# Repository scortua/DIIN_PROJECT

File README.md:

# Proyecto CNC para Cuidado de Plantulas en Vivero

Este proyecto consiste en desarrollar una máquina CNC capaz de cuidar plantulas en un vivero, utilizando motores, materiales reciclables y económicos, incorporando inteligencia artificial y sensores.

## Objetivos
- Automatizar tareas de cuidado en el vivero.
- Optimizar el uso de recursos utilizando materiales reciclables y de bajo costo.
- Integrar sensores para monitorear las condiciones ambientales y de crecimiento de las plantulas.
- Utilizar técnicas de IA para la toma de decisiones en tiempo real.

## Componentes Principales

### Hardware
- **Motores y actuadores:** Responsables del movimiento y la acción precisa en el cuidado de las plantulas.
- **Sensores:** 
    - Sensores de humedad y temperatura para medir las condiciones ambientales.
    - Sensores de luz para asegurar niveles adecuados de iluminación.
- **Materiales reciclables:** Estructuras y componentes fabricados con materiales reutilizados y económicos.
    
### Software
- **Control CNC:** Algoritmos para la operación y movimiento controlado de la máquina.
- **Inteligencia Artificial:** 
    - Procesamiento de datos de sensores.
    - Toma de decisiones automáticas para mejorar el crecimiento de las plantulas.
- **Interfaz de usuario:** Herramienta para monitorear y configurar el sistema en tiempo real.

## Funcionamiento del Sistema

1. **Monitoreo:**  
     Los sensores recogen datos sobre humedad, temperatura y luz.  
2. **Análisis:**  
     La IA analiza la información recopilada para identificar las necesidades de cada plantula.
3. **Acción:**  
     El CNC ejecuta movimientos precisos para crear condiciones óptimas: ajustar la dosificación de agua, mover elementos o modificar la iluminación.
4. **Retroalimentación:**  
     El sistema ajusta sus acciones de forma continua, basándose en los datos en tiempo real.

## Beneficios
- Fomenta el uso de tecnologías sostenibles.
- Aumenta la eficiencia en el cuidado de plantulas.
- Reduce costos mediante el uso de materiales reciclables y componentes económicos.
- Optimiza el crecimiento y la salud de las plantas a través de decisiones basadas en datos.

Este proyecto representa un avance significativo en la integración de la robótica y la inteligencia artificial en la agricultura, proporcionando soluciones innovadoras y sostenibles para el cuidado de viveros.

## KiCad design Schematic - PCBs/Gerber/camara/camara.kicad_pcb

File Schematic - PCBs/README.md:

# Proyecto DIIN
 En este repositorio se encontrara los esquematicos, diseño de PCB's,  programas, etc; sobre el proyecto de CNC que cuide plantulas.

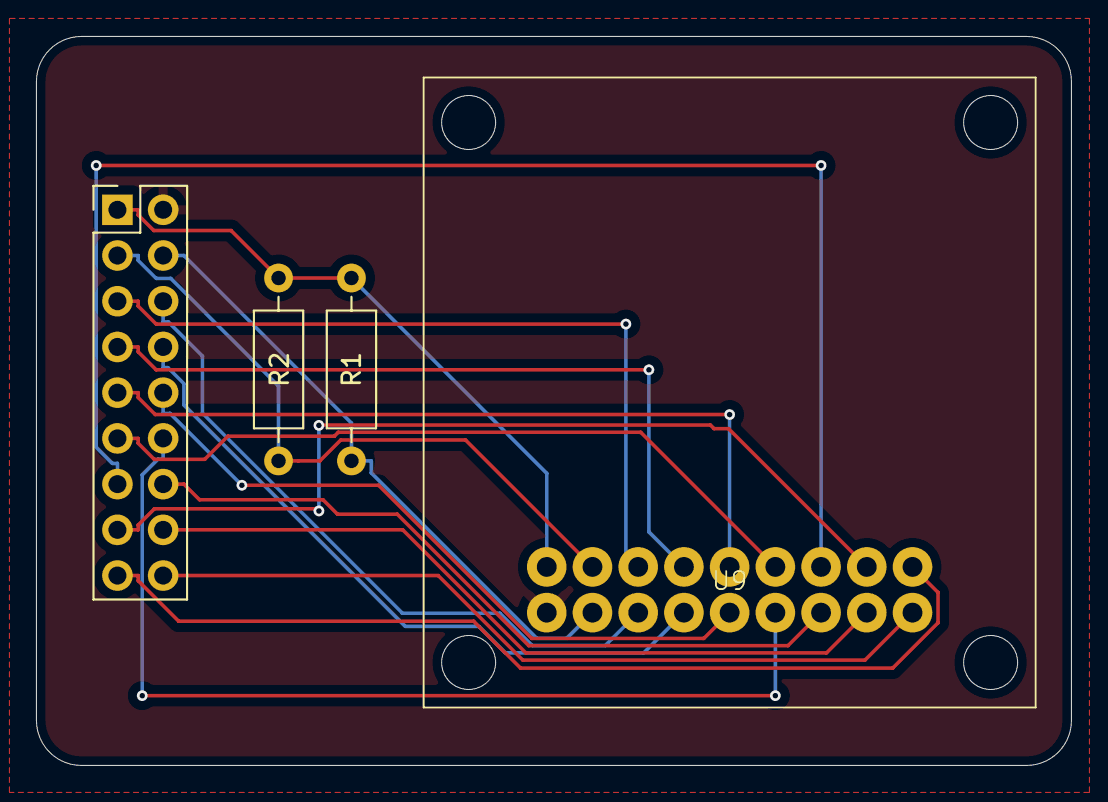
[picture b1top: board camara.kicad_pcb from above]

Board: 2 copper layers, 57.5 x 40.5 mm, 4 parts (0 on the bottom side), 18 nets.

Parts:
J1: Conn_02x09_Odd_Even; PinHeader_2x09_P2.54mm_Vertical
R1, R2: 4.7k; R_Axial_DIN0207_L6.3mm_D2.5mm_P10.16mm_Horizontal
U9: OV7670

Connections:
+3.3V: J1.1, R1.1, R2.1, U9.1 (+3.3V)
D0: J1.16, U9.16 (D0)
D1: J1.15, U9.15 (D1)
D2: J1.14, U9.14 (D2)
D3: J1.13, U9.13 (D3)
D4: J1.12, U9.12 (D4)
D5: J1.11, U9.11 (D5)
D6: J1.10, U9.10 (D6)
D7: J1.9, U9.9 (D7)
GND: J1.2, U9.2 (GND)
HREF: J1.6, U9.6 (HREF)
PCLK: J1.7, U9.7 (PCLK)
PWDN: J1.18, U9.18 (PWDN)
RESET: J1.17, U9.17 (RESET)
SOIC: J1.3, R2.2, U9.3 (SOIC)
SOID: J1.4, R1.2, U9.4 (SOID)
VSYNC: J1.5, U9.5 (VSYNC)
XCLK: J1.8, U9.8 (XCLK)

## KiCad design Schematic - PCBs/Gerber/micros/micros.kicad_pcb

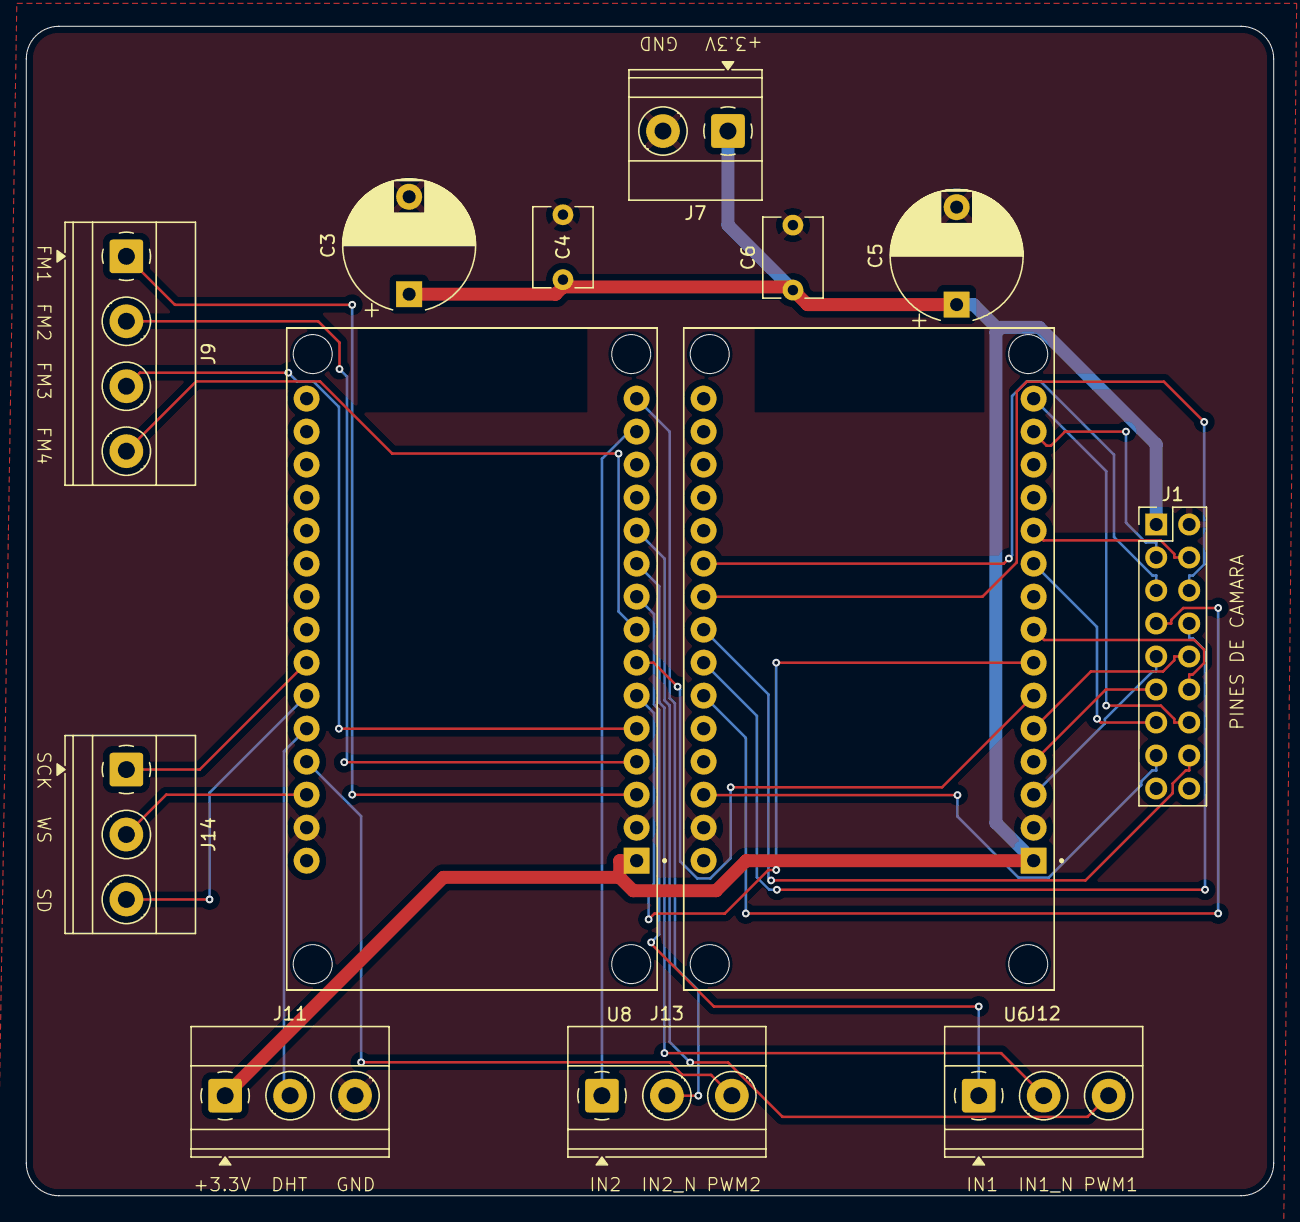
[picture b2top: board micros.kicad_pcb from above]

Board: 2 copper layers, 96.0 x 90.0 mm, 13 parts (0 on the bottom side), 32 nets.

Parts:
C3, C5: 10u; CP_Radial_D10.0mm_P7.50mm
C4, C6: 18n; C_Disc_D6.0mm_W4.4mm_P5.00mm
J1: Conn_02x09_Odd_Even; PinHeader_2x09_P2.54mm_Vertical
J7: Screw_Terminal_01x02; TerminalBlock_Phoenix_MKDS-1,5-2_1x02_P5.00mm_Horizontal
J9: Screw_Terminal_01x04; TerminalBlock_Phoenix_MKDS-1,5-4_1x04_P5.00mm_Horizontal
J11, J12, J13, J14: Screw_Terminal_01x03; TerminalBlock_Phoenix_MKDS-1,5-3_1x03_P5.00mm_Horizontal
U6, U8: ESP32-DEVKIT-V1; MODULE_ESP32_DEVKIT_V1

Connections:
+3.3V: C3.1, C4.1, C5.1, C6.1, J1.1, J7.1, J11.1, U6.1 (3V3), U8.1 (3V3)
D0: J1.16, U6.23 (D25)
D1: J1.15, U6.28 (D13)
D2: J1.14, U6.15 (D23)
D3: J1.13, U6.10 (D19)
D4: J1.12, U6.8 (D5)
D5: J1.11, U6.4 (D2)
D6: J1.10, U6.5 (D4)
D7: J1.9, U6.3 (D15)
DHT: J11.2, U8.26 (D14)
FM1: J9.1, U8.3 (D15)
FM2: J9.2, U8.4 (D2)
FM3: J9.3, U8.5 (D4)
FM4: J9.4, U8.8 (D5)
GND: C3.2, C4.2, C5.2, C6.2, J1.2, J7.2, J11.3, U6.2 (GND), U6.29 (GND), U8.2 (GND), U8.29 (GND)
HREF: J1.6, U6.22 (D33)
IN1: J12.1, U8.9 (D18)
IN1_N: J12.2, U8.10 (D19)
IN2: J13.1, U8.14 (D22)
IN2_N: J13.2, U8.15 (D23)
PCLK: J1.7, U6.25 (D27)
PWM1: J12.3, U8.11 (D21)
PWM2: J13.3, U8.27 (D12)
RX: U6.6 (RX2), U8.7 (TX2)
SCK: J14.1, U8.24 (D26)
SD: J14.3, U8.25 (D27)
SOIC: J1.3, U6.14 (D22)
SOID: J1.4, U6.11 (D21)
TX: U6.7 (TX2), U8.6 (RX2)
VSYNC: J1.5, U6.21 (D32)
WS: J14.2, U8.28 (D13)
XCLK: J1.8, U6.24 (D26)

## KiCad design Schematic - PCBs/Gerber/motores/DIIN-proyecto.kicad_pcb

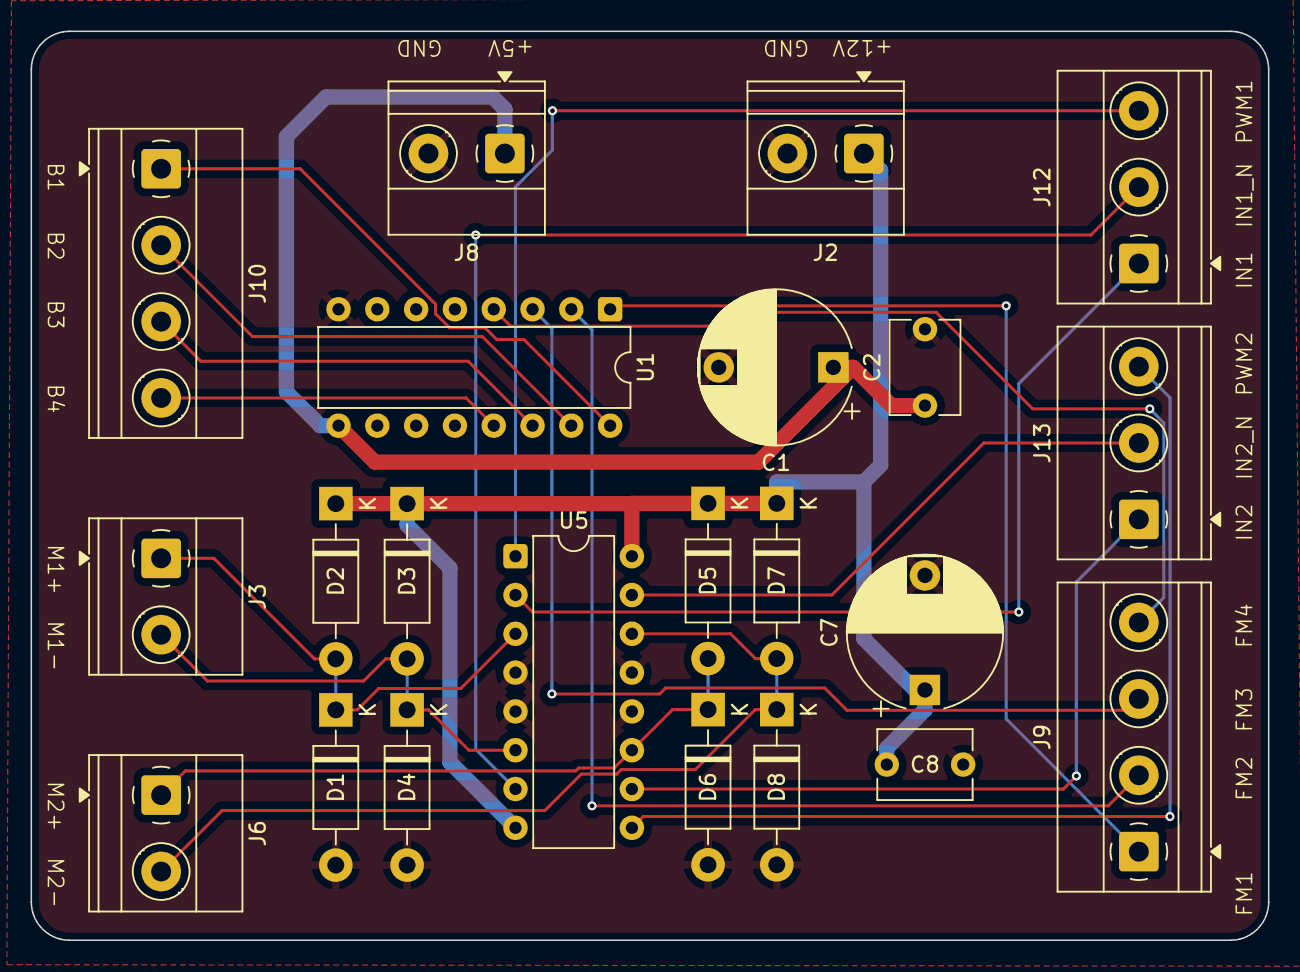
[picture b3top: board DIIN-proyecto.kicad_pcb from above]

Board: 2 copper layers, 81.0 x 59.5 mm, 22 parts (0 on the bottom side), 21 nets.

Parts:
C1, C7: 10u; CP_Radial_D10.0mm_P7.50mm
C2, C8: 18n; C_Disc_D6.0mm_W4.4mm_P5.00mm
D1, D2, D3, D4, D5, D6, D7, D8: 1N4004; D_DO-41_SOD81_P10.16mm_Horizontal
J2, J3, J6, J8: Screw_Terminal_01x02; TerminalBlock_Phoenix_MKDS-1,5-2_1x02_P5.00mm_Horizontal
J9, J10: Screw_Terminal_01x04; TerminalBlock_Phoenix_MKDS-1,5-4_1x04_P5.00mm_Horizontal
J12, J13: Screw_Terminal_01x03; TerminalBlock_Phoenix_MKDS-1,5-3_1x03_P5.00mm_Horizontal
U1: ULN2003A; DIP-16_W7.62mm
U5: L293D; DIP-16_W7.62mm

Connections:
+12V: C7.1, C8.1, D2.1 (K), D3.1 (K), D5.1 (K), D7.1 (K), J2.1, U5.8 (VCC2), U5.16 (VCC1)
B1: J10.1, U1.16 (O1)
B2: J10.2, U1.15 (O2)
B3: J10.3, U1.14 (O3)
B4: J10.4, U1.13 (O4)
COM: C1.1, C2.1, J8.1, U1.9 (COM)
FM1: J9.1, U1.1 (I1)
FM2: J9.2, U1.2 (I2)
FM3: J9.3, U1.3 (I3)
FM4: J9.4, U1.4 (I4)
GND: C1.2, C2.2, C7.2, C8.2, D1.2 (A), D4.2 (A), D6.2 (A), D8.2 (A), J2.2, J8.2, U1.8 (GND), U5.4 (GND), U5.5 (GND), U5.12 (GND), U5.13 (GND)
IN1: J12.1, U5.2 (1A)
IN1_N: J12.2, U5.7 (2A)
IN2: J13.1, U5.10 (3A)
IN2_N: J13.2, U5.15 (4A)
PWM1: J12.3, U5.1 (EN1,2)
PWM2: J13.3, U5.9 (EN3,4)
X1: D1.1 (K), D2.2 (A), J3.1, U5.3 (1Y)
X2: D3.2 (A), D4.1 (K), J3.2, U5.6 (2Y)
Y1: D5.2 (A), D6.1 (K), J6.1, U5.11 (3Y)
Y2: D7.2 (A), D8.1 (K), J6.2, U5.14 (4Y)

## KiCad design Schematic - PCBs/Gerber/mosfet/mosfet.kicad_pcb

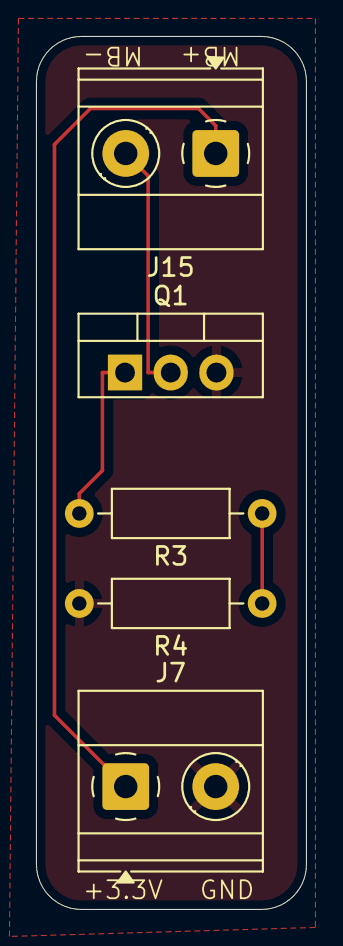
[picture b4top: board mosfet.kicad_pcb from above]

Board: 2 copper layers, 15.0 x 48.5 mm, 5 parts (0 on the bottom side), 5 nets.

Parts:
J7, J15: Screw_Terminal_01x02; TerminalBlock_Phoenix_MKDS-1,5-2_1x02_P5.00mm_Horizontal
Q1: IRF540N; TO-220-3_Vertical
R3, R4: 5.1k; R_Axial_DIN0207_L6.3mm_D2.5mm_P10.16mm_Horizontal

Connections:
+3.3V: J7.1, J15.1
GND: J7.2, Q1.3 (S), R4.2
MB-: J15.2, Q1.2 (D)
MBE: R3.1, R4.1
unnamed: Q1.1 (G), R3.2

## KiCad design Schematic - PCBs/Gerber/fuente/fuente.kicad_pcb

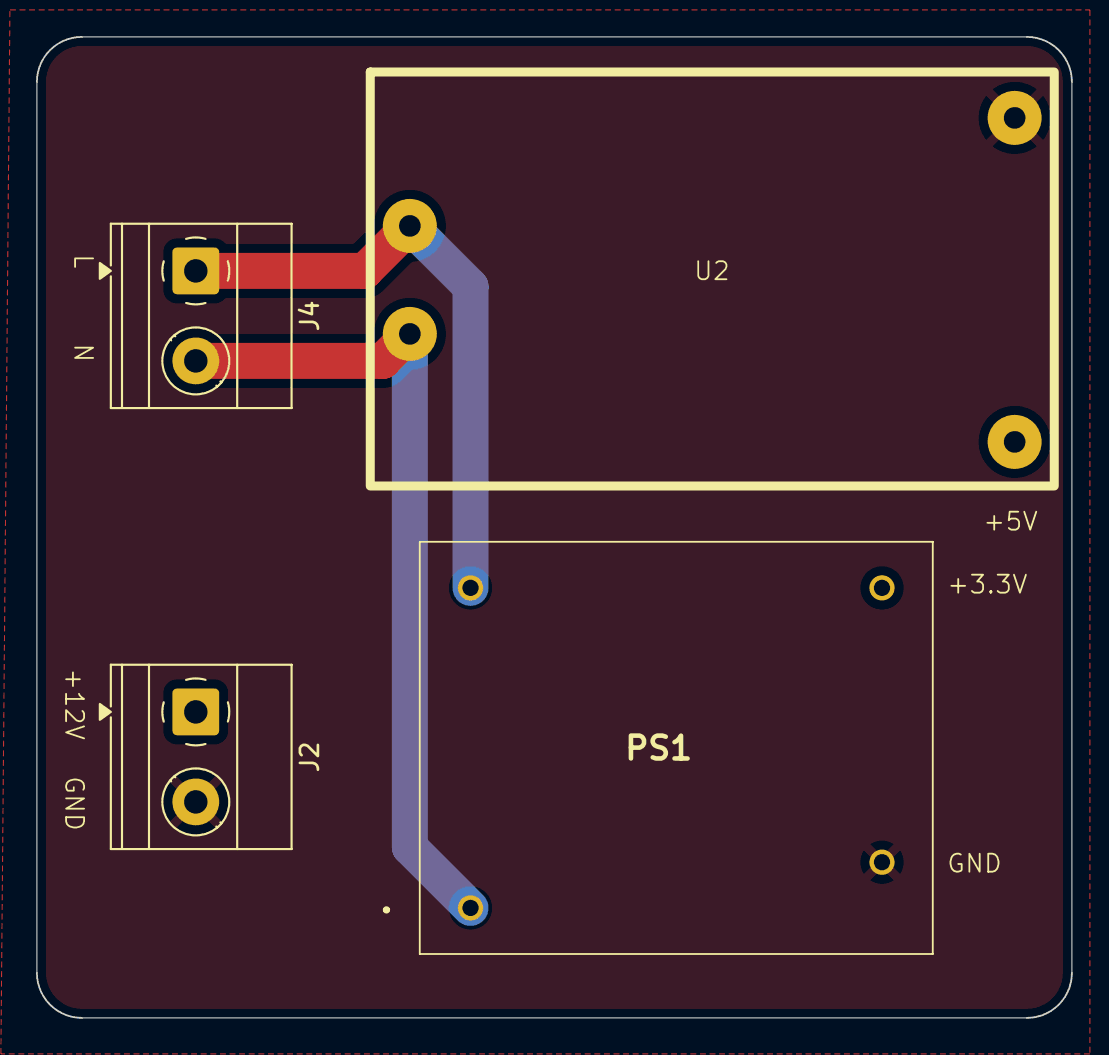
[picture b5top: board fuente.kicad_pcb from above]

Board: 2 copper layers, 57.5 x 54.5 mm, 4 parts (0 on the bottom side), 3 nets.

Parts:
J2, J4: Screw_Terminal_01x02; TerminalBlock_Phoenix_MKDS-1,5-2_1x02_P5.00mm_Horizontal
PS1: RAC03-3.3SK; RAC0305SK
U2: HLK-5M03; HLK5M03

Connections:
GND: J2.2, PS1.2 (-VOUT), U2.3 (GND)
L: J4.1, PS1.4 (VAC_IN_(N)), U2.1 (L)
N: J4.2, PS1.1 (VAC_IN_(L)), U2.2 (N)

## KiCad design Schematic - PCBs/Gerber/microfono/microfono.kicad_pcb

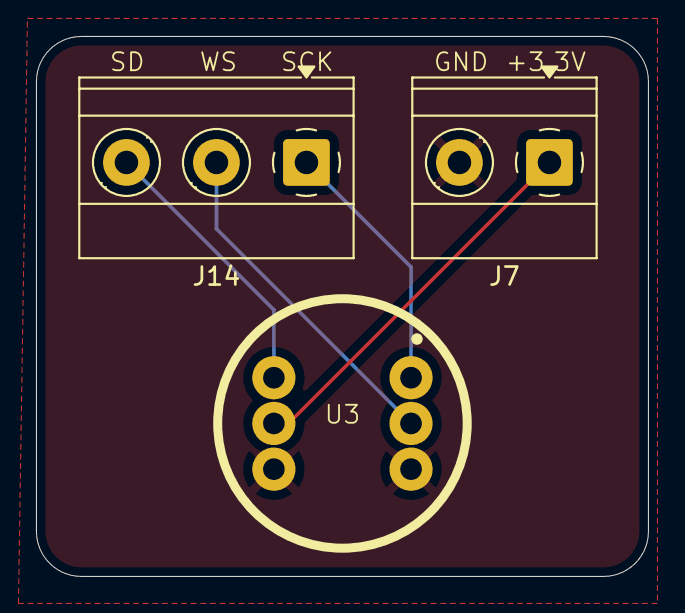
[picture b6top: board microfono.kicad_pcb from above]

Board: 2 copper layers, 34.0 x 30.0 mm, 3 parts (0 on the bottom side), 5 nets.

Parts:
J7: Screw_Terminal_01x02; TerminalBlock_Phoenix_MKDS-1,5-2_1x02_P5.00mm_Horizontal
J14: Screw_Terminal_01x03; TerminalBlock_Phoenix_MKDS-1,5-3_1x03_P5.00mm_Horizontal
U3: INMP441

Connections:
+3.3V: J7.1, U3.5 (VDD)
GND: J7.2, U3.3 (L/R), U3.6 (GND)
SCK: J14.1, U3.1 (SCK)
SD: J14.3, U3.4 (SD)
WS: J14.2, U3.2 (WS)

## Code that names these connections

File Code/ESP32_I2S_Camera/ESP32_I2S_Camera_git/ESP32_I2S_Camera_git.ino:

#include "OV7670.h"
#include <WiFi.h>
#include <WiFiMulti.h>
#include <WiFiClient.h>
#include "BMP.h"

const int SIOD = 21; // SDA
const int SIOC = 22; // SCL

const int VSYNC = 34;
const int HREF = 35;

const int XCLK = 32;
const int PCLK = 33;

const int D0 = 27;
const int D1 = 17;
const int D2 = 16;
const int D3 = 15;
const int D4 = 14;
const int D5 = 13;
const int D6 = 12;
const int D7 = 4;

#define ssid1     "Familia montañez"
#define password1 "Tomashilda243"

OV7670 *camera;
WiFiMulti wifiMulti;
WiFiServer server(80);
unsigned char bmpHeader[BMP::headerSize];

void serve()
{
  WiFiClient client = server.available();
  if (!client) return;

  String req = client.readStringUntil('\r');
  client.read(); // consume '\n'

  if (req.indexOf("GET /camera") >= 0) {
    camera->oneFrame();
    client.println("HTTP/1.1 200 OK");
    client.println("Content-type: image/bmp");
    client.println("Connection: close");
    client.println();
    client.write(bmpHeader, BMP::headerSize);
    client.write(camera->frame, camera->xres * camera->yres * 2);
  } else {
    client.println("HTTP/1.1 200 OK");
    client.println("Content-type: text/html");
    client.println("Connection: close");
    client.println();
    client.print(
      "<style>body{margin:0} img{height:100%;width:auto}</style>"
      "<img id='a' src='/camera' onload='this.style.display=\"initial\"; var b=document.getElementById(\"b\"); b.style.display=\"none\"; b.src=\"/camera?\"+Date.now();'>"
      "<img id='b' style='display:none' src='/camera' onload='this.style.display=\"initial\"; var a=document.getElementById(\"a\"); a.style.display=\"none\"; a.src=\"/camera?\"+Date.now();'>"
    );
  }

  delay(1);
  client.stop();
}

void setup() 
{
  Serial.begin(115200);

  wifiMulti.addAP(ssid1, password1);
  Serial.println("Connecting Wifi...");
  while (wifiMulti.run() != WL_CONNECTED) {
    delay(500);
    Serial.print(".");
  }

  Serial.println("\nWiFi connected");
  Serial.println("IP address: ");
  Serial.println(WiFi.localIP());

  camera = new OV7670(OV7670::Mode::QQVGA_RGB565, SIOD, SIOC, VSYNC, HREF, XCLK, PCLK, D0, D1, D2, D3, D4, D5, D6, D7);
  BMP::construct16BitHeader(bmpHeader, camera->xres, camera->yres);

  server.begin();
}

void loop()
{
  serve();
  camera->oneFrame();
}

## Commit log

2025-03-12 MADE creación del repositorio
2025-03-30 ADD modelos detallados y funcionales
2025-04-12 ADD implementaciones de actuadores
2025-04-21 ADD codigo probar motores
2025-04-22 UPDATE prueba server
2025-04-24 UPDATE codigo de prueba web y uso de micro
2025-05-01 UPDATE base para poder usar botones y motores
2025-05-02 UPDATE usar motores y visualizacion web
2025-05-07 UPDATE sistema funcional
2025-05-07 UPDATE momento final
2025-05-30 LAST UPDATE
